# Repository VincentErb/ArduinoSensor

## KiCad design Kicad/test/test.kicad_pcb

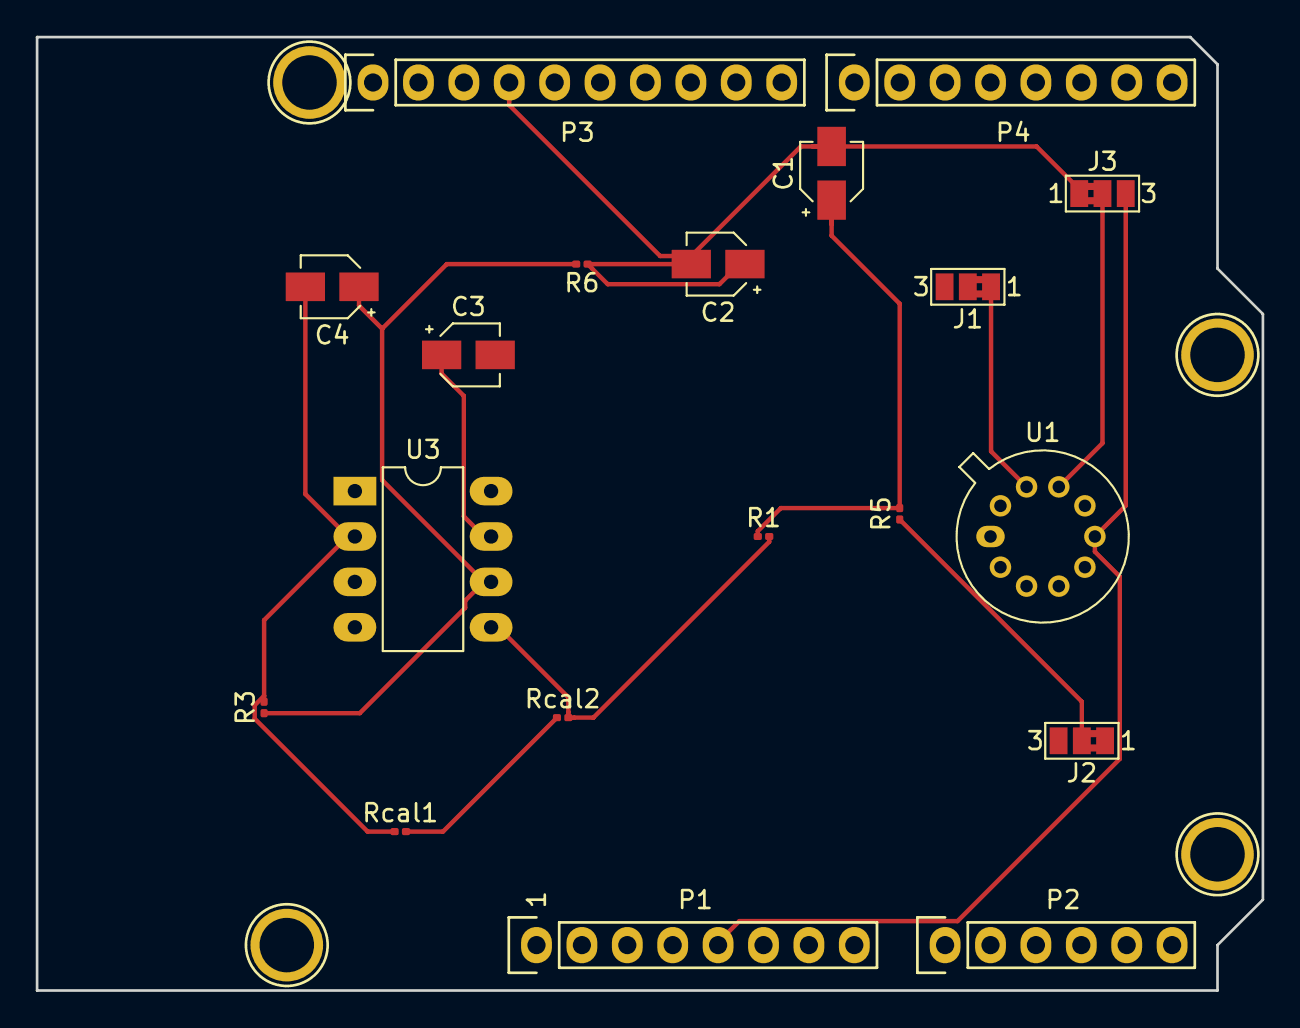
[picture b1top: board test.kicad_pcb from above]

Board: 2 copper layers, 68.6 x 53.3 mm, 23 parts (0 on the bottom side), 16 nets.

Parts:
C1, C2, C3: 100n; CP_Elec_3x5.3
C4: 1µ; CP_Elec_3x5.3
J1, J2, J3: Conn_01x03; SolderJumper-3_P1.3mm_Bridged2Bar12_Pad1.0x1.5mm_NumberLabe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
P1: Power; Socket_Strip_Arduino_1x08
P2: Analog; Socket_Strip_Arduino_1x06
P3: Digital; Socket_Strip_Arduino_1x10
P4: Digital; Socket_Strip_Arduino_1x08
P5, P6, P7, P8: CONN_01X01; Arduino_1pin
R1, R3: 100k; R_0201_0603Metric
R5: 10k; R_0201_0603Metric
R6: 1k; R_0201_0603Metric
Rcal1, Rcal2: 33; R_0201_0603Metric
U1: Gaz_sensor; TO-5-10
U3: LTC1050; DIP-8_W7.62mm_LongPads

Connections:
+3V3: J1.2, P1.4
+5V: C3.1, J3.3, P1.5, U1.6, U3.7
/A1: P2.2, U1.1
/A2: C2.1, P2.3, R6.1
/A4(SDA): P2.5, P3.2
/A5(SCL): P2.6, P3.1
/Gs1_out: J2.3, U1.2
/Gs2_in: J1.1, U1.9
/Gs2_out: J2.1, U1.7
/Hr_in: J3.2, U1.8
/Rsensor: J2.2, R5.1
GND: C1.2, C2.2, C3.2, J3.1, P1.6, P1.7, P3.4, R1.2, Rcal2.2, U1.3, U3.4, U3.5
unnamed: C1.1, R1.1, R5.2, U3.3
unnamed: C4.1, R3.1, R6.2, U3.6
unnamed: C4.2, R3.2, Rcal1.1, U3.2
unnamed: Rcal1.2, Rcal2.1

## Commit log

2019-11-18 first example TX OK
2019-11-19 interrupt ok PIN2
2019-11-22 add power saving
2019-12-02 put kidad project
2020-01-22 add kicad changes
